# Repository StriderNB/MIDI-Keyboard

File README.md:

# MIDI-Keyboard
Week 3 project of Half Life event hosted by Hack Club.

# Features
A Midi Keyboard in the shape of a star!

3 Switches with shine through rgb SK6812MINI-E Neopixels

2 Slide potentiometers

A clickable 360 degree rotary encoder

Controlled and powered by a Waveshare ESP32-S3-Zero

# Setup
1. Install CircuitPython on the ESP32-S3 ZERO
2. Install KMK and adafruit and neopixel libraries
3. Save the boot.py file in the root of the CIRCUITPY drive
4. Save the code.py file onto the drive
5. Open any DAW and select the Midi device

# Controls
| Button | Function |
| :--- | :---: |
| Touch 1-6 | Plays a note |
| Switch 1 | Turns on sustain |
| Switch 2 | Turns the touch buttons down an octave |
| Switch 3 | Turns the touch buttons up an octave |
| Slider 1 | Filter cutoff |
| Slider 2 | Reverb | 
| Rotary Encoder | Turns volume up or down |
| Rotary Encoder Button | Turns off the led RGB |

# BOM
| Item | Qty | Supplier | Cost/item | Total Cost | Link |
| :--- | :---: | :--- | :---: | :---: | :--- |
| SK6812MINI-E | 10 | Aliexpress | $0.36 | $3.60 | [Link](https://www.aliexpress.us/item/3256807677321116.html?spm=a2g0o.cart.0.0.1f5c38da4NfrhP&mp=1&pdp_npi=6%40dis%21USD%21USD+3.61%21USD+3.61%21%21USD+3.61%21%21%21%4021030dcd17929017765575367e0f08%2112000042594617264%21ct%21US%218321405938%21%211%210%21&_gl=1*12w1jau*_gcl_aw*R0NMLjE3OTI5MDE2MzAuQ2owS0NRandydkhXQmhES0FSSXNBQm1wN2gxLVVCZjU0a2JLd012Mlkya0pxbDRXSDNaMlBoOU5SYVVBTk5SSXRMaWw1bFJrbXpXZzZJNGFBcFBLRUFMd193Y0I.*_gcl_dc*R0NMLjE3OTI5MDE2MzAuQ2owS0NRandydkhXQmhES0FSSXNBQm1wN2gxLVVCZjU0a2JLd012Mlkya0pxbDRXSDNaMlBoOU5SYVVBTk5SSXRMaWw1bFJrbXpXZzZJNGFBcFBLRUFMd193Y0I.*_gcl_au*MjEyNDg5MTc2NC4xNzkwNTM4MDQ3*_ga*NDE0NzUzODY3LjE3OTI2OTUyMjg.*_ga_VED1YSGNC7*czE3OTI5NjM5NzEkbzYkZzEkdDE3OTI5NjQ0MDUkajUzJGwwJGgw&gatewayAdapt=glo2usa) |
| Bourns Slider | 2 | AliExpress | $3.00 | $6.00 | [Link](https://www.aliexpress.us/item/3256808527031041.html?spm=a2g0o.cart.0.0.1f5c38da4NfrhP&mp=1&pdp_npi=6%40dis%21USD%21USD+2.99%21USD+2.99%21%21USD+2.99%21%21%21%4021030dcd17929017765575367e0f08%2112000046545295125%21ct%21US%218321405938%21%212%210%21&_gl=1*ppe06u*_gcl_aw*R0NMLjE3OTI5MDE2MzAuQ2owS0NRandydkhXQmhES0FSSXNBQm1wN2gxLVVCZjU0a2JLd012Mlkya0pxbDRXSDNaMlBoOU5SYVVBTk5SSXRMaWw1bFJrbXpXZzZJNGFBcFBLRUFMd193Y0I.*_gcl_dc*R0NMLjE3OTI5MDE2MzAuQ2owS0NRandydkhXQmhES0FSSXNBQm1wN2gxLVVCZjU0a2JLd012Mlkya0pxbDRXSDNaMlBoOU5SYVVBTk5SSXRMaWw1bFJrbXpXZzZJNGFBcFBLRUFMd193Y0I.*_gcl_au*MjEyNDg5MTc2NC4xNzkwNTM4MDQ3*_ga*NDE0NzUzODY3LjE3OTI2OTUyMjg.*_ga_VED1YSGNC7*czE3OTI5NjM5NzEkbzYkZzEkdDE3OTI5NjQ0MDkkajQ5JGwwJGgw&gatewayAdapt=glo2usa) |
| Rotary Encoder | 1 | AliExpress | $1.55 | $1.55 | [Link](https://www.aliexpress.us/item/3256807457768762.html?spm=a2g0o.cart.0.0.1f5c38da4NfrhP&mp=1&pdp_npi=6%40dis%21USD%21USD+1.55%21USD+1.55%21%21USD+1.55%21%21%21%4021030dcd17929017765575367e0f08%2112000041630839427%21ct%21US%218321405938%21%211%210%21&_gl=1*10wpaba*_gcl_aw*R0NMLjE3OTI5MDE2MzAuQ2owS0NRandydkhXQmhES0FSSXNBQm1wN2gxLVVCZjU0a2JLd012Mlkya0pxbDRXSDNaMlBoOU5SYVVBTk5SSXRMaWw1bFJrbXpXZzZJNGFBcFBLRUFMd193Y0I.*_gcl_dc*R0NMLjE3OTI5MDE2MzAuQ2owS0NRandydkhXQmhES0FSSXNBQm1wN2gxLVVCZjU0a2JLd012Mlkya0pxbDRXSDNaMlBoOU5SYVVBTk5SSXRMaWw1bFJrbXpXZzZJNGFBcFBLRUFMd193Y0I.*_gcl_au*MjEyNDg5MTc2NC4xNzkwNTM4MDQ3*_ga*NDE0NzUzODY3LjE3OTI2OTUyMjg.*_ga_VED1YSGNC7*czE3OTI5NjM5NzEkbzYkZzEkdDE3OTI5NjQ0MDMkajU1JGwwJGgw&gatewayAdapt=glo2usa) |
| Waveshare ESP32-S3-ZERO | 1 | AliExpress | $4.32 | $4.32 | [Link](https://www.aliexpress.us/item/3256807949476561.html?spm=a2g0o.cart.0.0.1f5c38da4NfrhP&mp=1&pdp_npi=6%40dis%21USD%21USD+4.32%21USD+4.32%21%21USD+4.32%21%21%21%4021030dcd17929017765575367e0f08%2112000051614441514%21ct%21US%218321405938%21%211%210%21&_gl=1*10wpaba*_gcl_aw*R0NMLjE3OTI5MDE2MzAuQ2owS0NRandydkhXQmhES0FSSXNBQm1wN2gxLVVCZjU0a2JLd012Mlkya0pxbDRXSDNaMlBoOU5SYVVBTk5SSXRMaWw1bFJrbXpXZzZJNGFBcFBLRUFMd193Y0I.*_gcl_dc*R0NMLjE3OTI5MDE2MzAuQ2owS0NRandydkhXQmhES0FSSXNBQm1wN2gxLVVCZjU0a2JLd012Mlkya0pxbDRXSDNaMlBoOU5SYVVBTk5SSXRMaWw1bFJrbXpXZzZJNGFBcFBLRUFMd193Y0I.*_gcl_au*MjEyNDg5MTc2NC4xNzkwNTM4MDQ3*_ga*NDE0NzUzODY3LjE3OTI2OTUyMjg.*_ga_VED1YSGNC7*czE3OTI5NjM5NzEkbzYkZzEkdDE3OTI5NjQ0MDMkajU1JGwwJGgw&gatewayAdapt=glo2usa) |
| Keycaps | 10 | AliExpress | $0.30 | $3.00 | [Link](https://www.aliexpress.us/item/3256809178113894.html?spm=a2g0o.cart.0.0.1f5c38da4NfrhP&mp=1&pdp_npi=6%40dis%21USD%21USD+3.03%21USD+3.03%21%21USD+3.03%21%21%21%4021030dcd17929017765575367e0f08%2112000048873877375%21ct%21US%218321405938%21%211%210%21&_gl=1*ndrp7t*_gcl_aw*R0NMLjE3OTI5MDE2MzAuQ2owS0NRandydkhXQmhES0FSSXNBQm1wN2gxLVVCZjU0a2JLd012Mlkya0pxbDRXSDNaMlBoOU5SYVVBTk5SSXRMaWw1bFJrbXpXZzZJNGFBcFBLRUFMd193Y0I.*_gcl_dc*R0NMLjE3OTI5MDE2MzAuQ2owS0NRandydkhXQmhES0FSSXNBQm1wN2gxLVVCZjU0a2JLd012Mlkya0pxbDRXSDNaMlBoOU5SYVVBTk5SSXRMaWw1bFJrbXpXZzZJNGFBcFBLRUFMd193Y0I.*_gcl_au*MjEyNDg5MTc2NC4xNzkwNTM4MDQ3*_ga*NDE0NzUzODY3LjE3OTI2OTUyMjg.*_ga_VED1YSGNC7*czE3OTI5NjM5NzEkbzYkZzEkdDE3OTI5NjQ1MjIkajU2JGwwJGgw&gatewayAdapt=glo2usa) |
| Switches | 10 | AliExpress | $0.20 | $2.00 | [Link](https://www.aliexpress.us/item/2251832663616399.html?spm=a2g0o.cart.0.0.1f5c38da4NfrhP&mp=1&pdp_npi=6%40dis%21USD%21USD+2.02%21USD+2.02%21%21USD+2.02%21%21%21%4021030dcd17929017765575367e0f08%2165277852476%21ct%21US%218321405938%21%211%210%21&_gl=1*6j82c4*_gcl_aw*R0NMLjE3OTI5MDE2MzAuQ2owS0NRandydkhXQmhES0FSSXNBQm1wN2gxLVVCZjU0a2JLd012Mlkya0pxbDRXSDNaMlBoOU5SYVVBTk5SSXRMaWw1bFJrbXpXZzZJNGFBcFBLRUFMd193Y0I.*_gcl_dc*R0NMLjE3OTI5MDE2MzAuQ2owS0NRandydkhXQmhES0FSSXNBQm1wN2gxLVVCZjU0a2JLd012Mlkya0pxbDRXSDNaMlBoOU5SYVVBTk5SSXRMaWw1bFJrbXpXZzZJNGFBcFBLRUFMd193Y0I.*_gcl_au*MjEyNDg5MTc2NC4xNzkwNTM4MDQ3*_ga*NDE0NzUzODY3LjE3OTI2OTUyMjg.*_ga_VED1YSGNC7*czE3OTI5NjM5NzEkbzYkZzEkdDE3OTI5NjQ2MDgkajU4JGwwJGgw&gatewayAdapt=glo2usa) |
| PCB | 1 | PCBWay | $5.00 | $5.00 | [Link](https://pcbway.com) |
| Estimated total shipping | 1 | | | $8.30 | |

#Additional Images

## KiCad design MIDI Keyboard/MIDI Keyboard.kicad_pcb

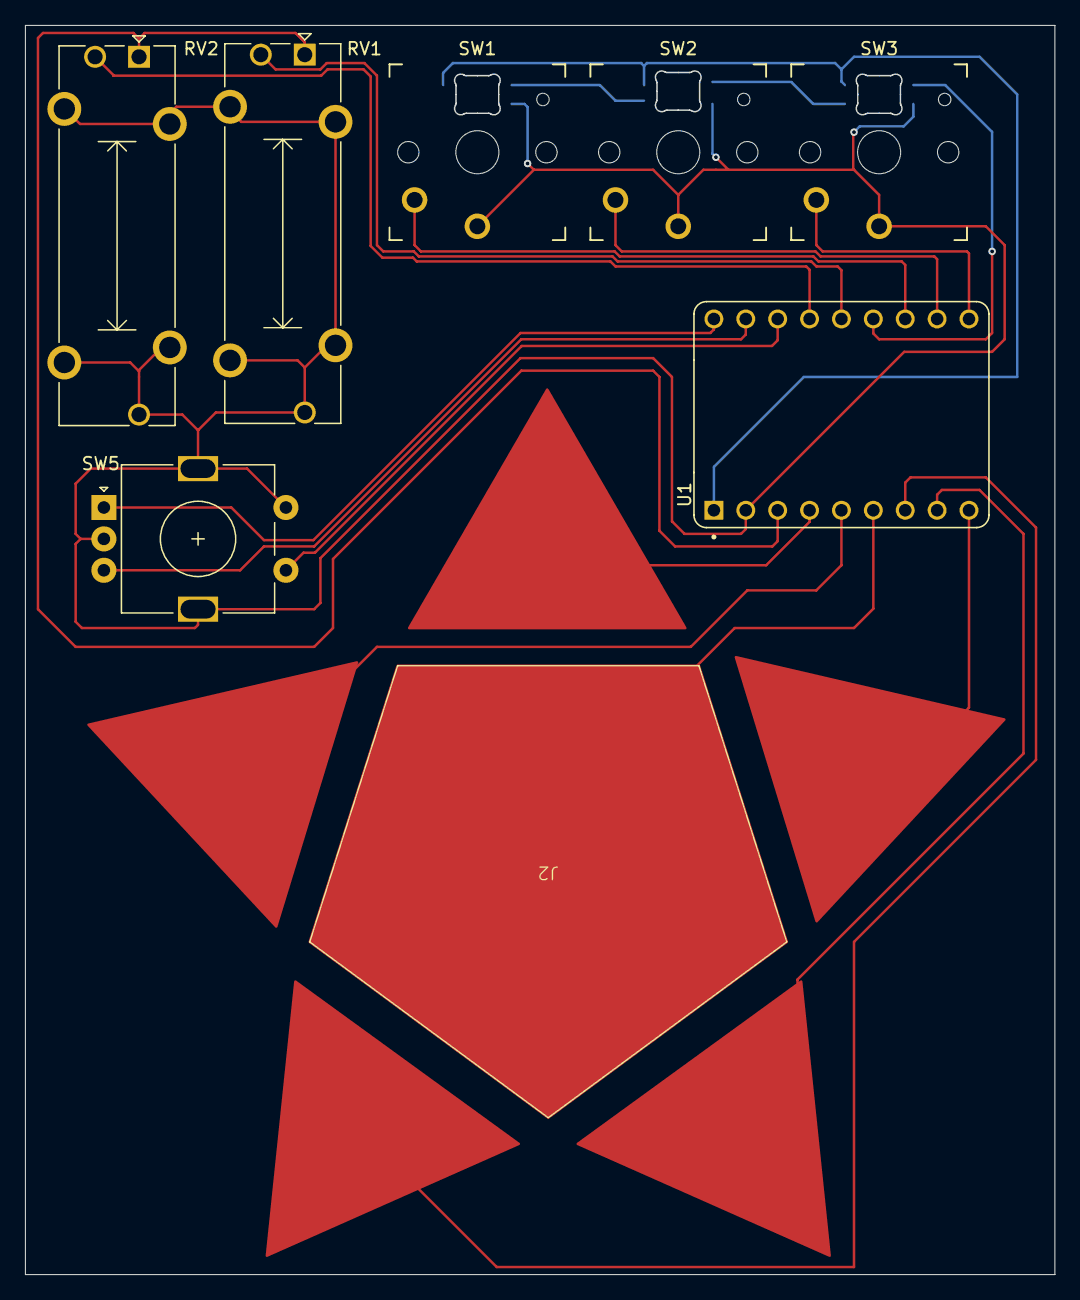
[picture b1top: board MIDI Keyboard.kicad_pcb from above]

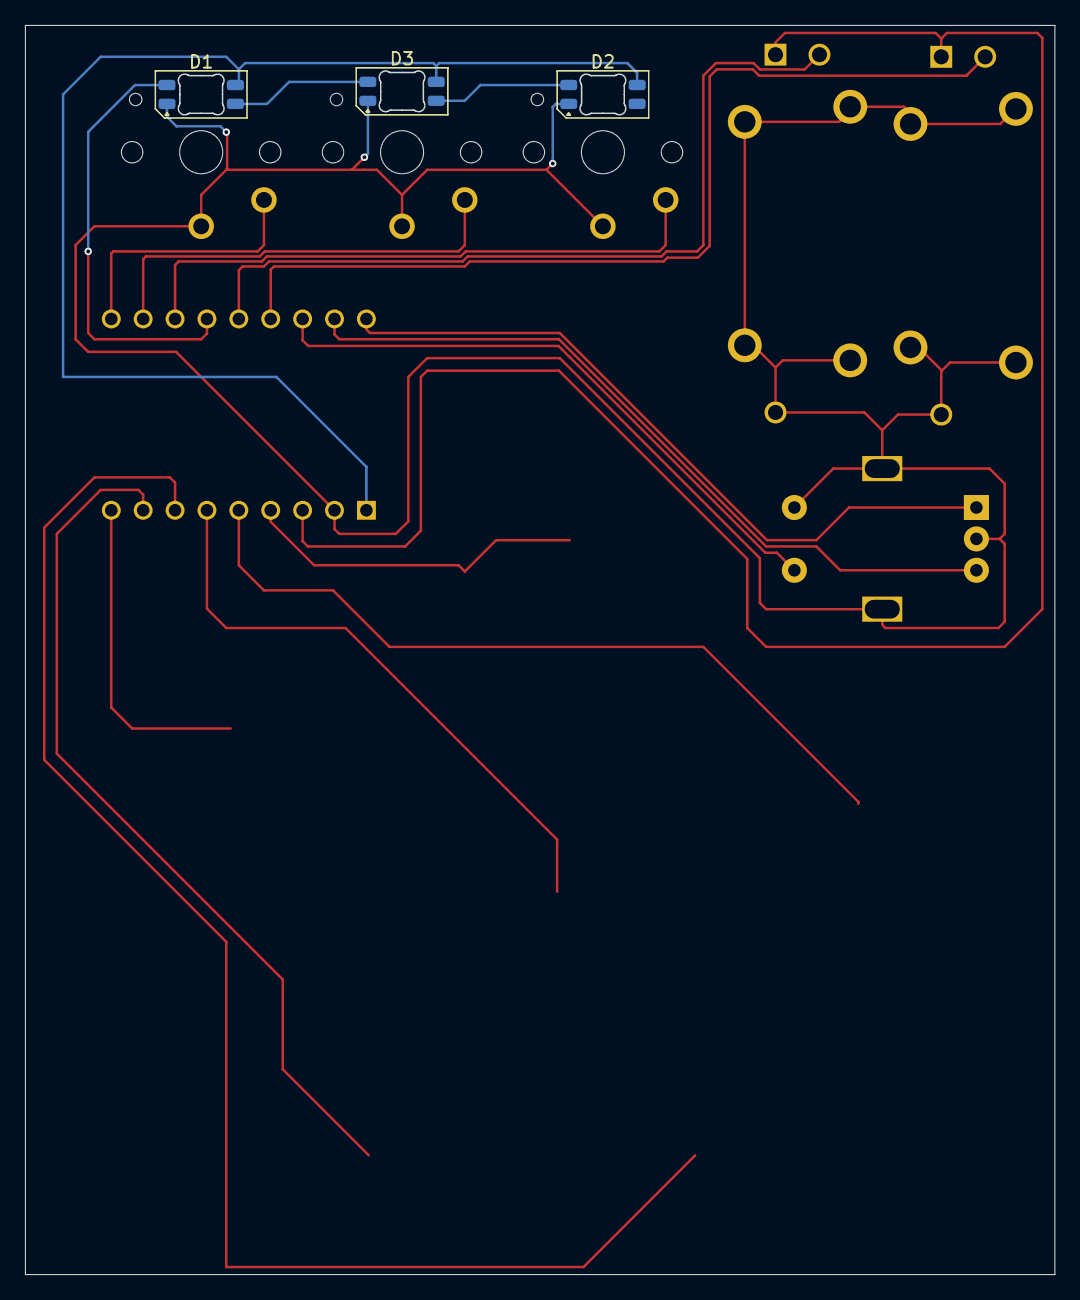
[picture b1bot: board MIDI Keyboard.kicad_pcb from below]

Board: 2 copper layers, 82.0 x 99.5 mm, 11 parts (3 on the bottom side), 20 nets.

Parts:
D1, D2, D3: SK6812MINI-E; LED_SK6812MINI-E_3.2x2.8mm_P1.5mm_ReverseMount
J2: Captive_Touch_Button; Star
RV1: RV1_Slider; Potentiometer_Bourns_PTA1543_Single_Slide
RV2: RV2_Slider; Potentiometer_Bourns_PTA1543_Single_Slide
SW1, SW2, SW3: SW_Push; Kailh Choc Low-Profile Switches
SW5: RotaryEncoder_Switch_MP; RotaryEncoder_Alps_EC11E-Switch_Vertical_H20mm
U1: Waveshare ESP32-S3-ZERO; Waveshare ESP32-S3-Zero

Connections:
+3V3: RV1.1, RV2.1, U1.3V3 (3V3(OUT))
+5V: D1.3 (VDD), D2.3 (VDD), D3.3 (VDD), U1.5V
/ENC1_A: SW5.A, U1.TX
/ENC1_B: SW5.B, U1.RX
/LED: D1.2 (DIN), U1.10 (GP10)
/Slide_1: RV1.2, U1.11 (GP11)
/Slide_2: RV2.2, U1.12 (GP12)
/Switch_1: SW1.2, U1.9 (GP9)
/Switch_2: SW2.2, U1.8 (GP8)
/Switch_3: SW3.2, U1.7 (GP7)
/Switch_4: SW5.S1, U1.13 (GP13)
/Touch_1: J2.1, U1.3 (GP3)
/Touch_2: J2.2, U1.1 (GP1)
/Touch_3: J2.3, U1.2 (GP2)
/Touch_4: J2.4, U1.4 (GP4)
/Touch_5: J2.5, U1.5 (GP5)
/Touch_6: J2.6, U1.6 (GP6)
GND: D1.1 (VSS), D2.1 (VSS), D3.1 (VSS), RV1.3, RV1.MP (MountPin), RV2.3, RV2.MP (MountPin), SW1.1, SW2.1, SW3.1, SW5.C, SW5.MP, SW5.S2, U1.GND
unnamed: D1.4 (DOUT), D3.2 (DIN)
unnamed: D2.2 (DIN), D3.4 (DOUT)

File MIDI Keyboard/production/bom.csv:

Designator,Footprint,Quantity,Value,LCSC Part #
"D1, D2, D3",LED_SK6812MINI-E_3.2x2.8mm_P1.5mm_ReverseMount,3,SK6812MINI-E,
J2,Star,1,Captive_Touch_Button,
RV1,Potentiometer_Bourns_PTA1543_Single_Slide,1,RV1_Slider,
RV2,Potentiometer_Bourns_PTA1543_Single_Slide,1,RV2_Slider,
"SW1, SW2, SW3",Kailh Choc Low-Profile Switches,3,SW_Push,
SW5,RotaryEncoder_Alps_EC11E-Switch_Vertical_H20mm,1,RotaryEncoder_Switch_MP,
U1,Waveshare ESP32-S3-Zero,1,Waveshare ESP32-S3-ZERO,
